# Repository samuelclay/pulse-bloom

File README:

<style>
#OB-pulse-bloom ol,
#OB-pulse-bloom ul {
    margin-left: 24px;
}
#OB-pulse-bloom li {
    color: inherit;
    font-size: inherit;
    list-style-position: outside;
}
#OB-pulse-bloom ol li {
    list-style-position: outside;
    list-style-type: decimal;
}
#OB-pulse-bloom img {
    margin: 24px auto;
    border: 1px solid #303030;
    display: block;
}
#OB-pulse-bloom img.small {
    float: left;
    margin-right: 24px;
}
#OB-pulse-bloom img.no-border {
    border: none;
}
#OB-pulse-bloom pre code {
    display: block;
    overflow-y: hidden;
}
</style>

<div id="OB-pulse-bloom">

This was my second year attending Burning Man. Many use Burning Man as a week to detach from their workweek and experience a new life of intense leisure. Not me, I come to Burning Man to build.

Pulse & Bloom is a [2014 honorarium installation](http://www.burningman.com/installations/art_honor.html). The core team of 6 people — [Saba Ghole](https://twitter.com/sabarani), [Shilo Shiv Suleman](https://twitter.com/shilo1221), [Rohan Dixit](https://twitter.com/rd108), [Heather Stewart](https://www.facebook.com/heather.stewart.3388), [Luke Iseman](https://twitter.com/liseman), and [myself](http://twitter.com/samuelclay) — built 20 interactive lotus flowers made out of steel and rowlux. Each lotus flower ranges from 8 to 18 feet tall, each of which lights up with your pulse. You and another person can put your hands on a couple of Hamsa hands at the base of the lotus flower and your respective heartbeats will light up the flower.

We've gotten some great press coverage at [the BBC](http://www.bbc.com/news/in-pictures-29059374), [The Guardian](http://www.theguardian.com/artanddesign/gallery/2014/sep/06/photography-new-york-fashion-gaza-islamic-state?CMP=fb_gu), [The Atlantic's Big Picture](http://www.theatlantic.com/infocus/2014/09/burning-man-2014/100802/#img07) [twice](http://www.theatlantic.com/infocus/2014/09/burning-man-2014/100802/#img22), [CBS News](http://www.cbsnews.com/pictures/burning-man-2014/9/), [NBC News](http://www.nbcnews.com/pop-culture/pop-culture-news/desert-dwellers-burning-man-festival-full-swing-n192541#ember903), and [MSNBC](http://on.msnbc.com/1qkUN4c).

As usual, the [complete source code for Pulse & Bloom is on GitHub](https://github.com/samuelclay/pulse-bloom).

### Your heartbeat in light

Here's a video of all twenty lotus flowers in full working order.

<video src="http://static.newsblur.com.s3.amazonaws.com/ofbrooklyn/Pulse%20%26%20Bloom.mp4" autoplay loop muted width="650"></video>

Each lotus flower is blue until a person or two sits down at its base and places their hand on the pulse sensor. You can see the Hamsa hand and its embedded pulse sensor in this shot of my girlfriend Brittany and me working on keeping the electronics going.

<h6 style="margin-top: -24px;text-align: right;">Photo credit Jim Urquhart / Reuters</h6>

When a pulse is read, the lotus flower shoots the heartbeat up the stem and into the petals, where it blooms in a brilliant display of amber. When two people's hands are being measured, both of their heartbeats are shown as two distinct colors.

## How the electronics are made

There are five stages to making the electronics:

 1. [Making the custom circuit boards](#boards)
 2. [Making the custom pulse sensors](#sensors)
 3. [Driving the high current LEDs](#leds)
 4. [Writing the firmware](#firmware)
 5. [Powering the lotuses](#power)

### 1. Making the custom circuit boards

The circuit board controls all of the lighting, sensors, timing, and debugging sequences. A reliable circuit board couldn't just be an Arduino and a breadboard. I decided to use [OSH Park](http://www.oshpark.com) and [OSH Stencils](http://www.oshstencils.com) to fabricate inexpensive circuit boards. I ultimately went through seven revisions while we worked out the final design of the lotuses. This included adding additional lights, additional sensors, controls for EL wire, and better power management using an external buck converter.

This board has support for multiple high current petal LEDs driven by digital RGB pins (used for fading colors in and out using PWM) and in multiple voltages. The high current petal LEDs runs on 12V, which comes directly off the battery, the ATmega328p chip and stem LEDs run at 5V, and the pulse sensor runs at 3.3V.

To convert 12V to 5V I use [a $3 switching voltage regulator from Electrodragon](http://www.electrodragon.com/product/better-than-lm2596-dc-dc-step-down-adjustable-power-supply-module/). This requires a +/- connection for both 12V in and 5V out. To convert 5V to 3.3V I used a linear voltage regulator soldered directly on the board, since the current requirements of the pulse sensor were around 20mA. The heat dissipated was negligible compared to the rest of the circuit.

I also added terminal connections for two 5 meter LEDs that wrapped around the tall lotus stem. We attached two 5 meter LED strips around the stems because when two people put their hands on the two pulse sensors, we need an easy way to show both heartbeats without one winning out over the other. When only one person's hand in being measured, both 5 meter light strips show the same color, which makes it that much brighter for a single person.

Lastly, the two pulse sensors terminate their I2C wires directly on the board. I used two separate I2C channels instead of one to cut down on time. I could easily have put both pulse sensors on the same I2C connections, but that would've required both pull-up resistors on the SDA and SCL data lines as well as a rewrite of the timing functions for the sensor.

All of these terminations are made using 2.5mm and 3.5mm pitch screw terminals. In hindsight I would have used female JST-SM mounted connectors and ordered custom wires with JST-SM male connectors. I assumed the lowest common denomenator would be bare tinned wire, but all of the bare wires could easily have been switched over to polarized, latching connectors. This would have reduced over 90% of the field work I had to perform on boards, as their wire would fall out of the screw terminals due to not being screwed in with enough force.

The board was laid out to be as big as a pack of gum. All of the 12V traces are thickened and isolated on the right side of the board. They are rated for 3 amps although they would end up only driving 1 amp on the playa.

These boards are then stenciled with solder paste and populated with their chips and passive components.

An inexpensive hot plate is used to reflow the solder. The chip is in a TQFP package, which has a 0.5mm pitch between pins. This makes it nearly impossible to hand solder. This stencil and reflow technique works well and my yield stayed high at around 95%.

Finally, the board is ready to be populated with screw terminals.

The final board in a dust-proof enclosure.

### 2. Making the custom pulse sensors

This was both the riskiest piece of the puzzle and also the most fun to build. In order to show your heartbeat on the lotus, I need to have a clear reading of your pulse. There are a fair number of issues with most off-the-shelf heartbeat sensors, including:

 * **Cost**: While a $50 pulse sensor is nice, it's way out of our budget. We spent $6 in components to make each of our pulse sensors for a total of 40 sensors (two per lotus).
 * **Design affordance**: There were a fair number of pulse sensors that required an infrared light on one side of your finger and an infrared detector/receiver on the other. This clamping of your finger wasn't something we could get away with in the desert. We needed a sensor you could just touch and hold on one side. It needed to be a simple interface so we wouldn't have to show any instructions.
 * **Reliability**: When a sensor gets covered in dust, will it still work? Infrared light, thankfully, passes through a layer of dust and can read the changes in blood flow in your finger. Some options were entirely visual and they would have performed quite poorly out on the playa.

The first prototype I built suffered from the design affordance and reliability issues, although it worked pretty well in ideal conditions.

<video src="http://static.newsblur.com.s3.amazonaws.com/ofbrooklyn/Pulse%20%26%20Bloom%20-%20Sensor%20opamp.mp4" autoplay loop muted width="650"></video>

We ended up finding an IC by Silicon Labs called the Si1143x, which uses three LEDs — two infrared and one visible — and a small QFN-10 sized light sensor.

I built out a small PCB the size of a fingertip.

This tiny IC is a bit tricky to solder as it has no leads and the pins are extremely close together. My yield dropped to about 80%, but 4 out of every 5 pulse sensors I built worked perfectly the first time. If they failed, I would remount them on the hot plate and try wicking away any solder bridges I could find. This worked only about half the time. After that I gave up and now have a plastic cup full of broken pulse sensors.

Finally the sensor is hooked up and a tiny red light is emitted, letting people know where to put their fingers.

### 3. Driving the high current LEDs

What turned these lotuses from flowers into gems are the high current LEDs mounted in the petals at the top. There are 9 of these high current LEDs per lotus, split into groups of three, each driven by a constant current driver. 

If you were to look at one of these LEDs from a few feet away, you would immediately see spots in your eyes. They are extremely bright pinpoints of light. The fact that they are also full color and need a heatsink due to their brightness means that you won't just find these in an easy package ready for plugging in.

<h6 style="margin-top: -24px;text-align: right;">Photo credit Jim Urquhart / Reuters</h6>

Normally a single LED is powered by a single constant current driver. This driver can drive up to 1A of current at 12V. Because we were only using a single channel of color (blue) in the rest state, which is where the lotus spent most of its time, we could triple the number of LEDs driven by a single constant current driver. 

When in use the petals glow amber, which uses two channels (100% red, 50% green) but only for a moment while at peak current. So while the peak current is above what this constant current driver is rated for, it's only at peak and therefore within our tolerance.

Using a Chinese distributor, we bought these Sparkfun high current LEDs for $0.86 each instead of the full $15. However, we also bought 80 of Sparkfun's PicoBucks to use as our constant current driver. While we could have built this ourselves to save money, buying 80 of something at $15 each is still only $1.2k, while building them ourselves would only have saved a few hundred dollars.

We bought 200 high current LEDs, all of which had to have their 6 anode and cathode connections soldered.

In order to connect 9 high current LEDs to the board, we need to drive them in groups of three. Each group has 6 connections: red, green, blue anodes, and red, green, blue cathodes. The wiring diagram for this setup can get a bit rats nesty, but the end result was fairly easy to work with, as the picobuck groups didn't cross.

Finally, a shot of a complete picobuck with the wire connectors in the background.

### 4. Writing the firmware

The [complete source code for Pulse & Bloom is on GitHub](https://github.com/samuelclay/pulse-bloom). There you can find the firmware used to program the main circuit board's ATmega328p chip, as well as designs for the laser cut cowl that sits over the pulse sensor's Si1143x IC. 

The easiest way to read the firmware is to dive into `src/pulse.cpp`. It has all of the pulse and rest states and handles the high level logic.

The state machine that runs the entire routine is determined by a couple of critical measurements. The program takes a measurement of both pulse sensors and determines whether a finger is covering either of them and whether or not that finger has an active pulse going.

    // Modes
    void determinePlayerMode();
    void determineFingerMode(int sensor1On, int sensor2On);
    void resetStem(PulsePlug *pulse);
    uint8_t adjustBpm(PulsePlug *pulse);
    
When there are no fingers on either of the pulse sensors, the program runs the rest state, which is a blue-topped lotus with a small blue snake running up and down the stem. The program is merely waiting for somebody to put their finger on a sensor.

    // State: resting
    void runResting();
    void runRestStem();
    void runRestStem(PulsePlug *pulse, int16_t currentLed);
    void clearStemLeds(PulsePlug *pulse);
    void beginPetalResting();
    bool runPetalResting();

Before a heartbeat is shown an accurate measurement of a heartbeat needs to be read. In order to determine whether a heartbeat is found and at what speed, a number of light detection measurements are taken and analyzed. I simply find the high frequency curve (the heartbeat) and the low frequency curve (the light sensors leveling out) and then use a simple peak and valley hueristic to determine the moment a heartbeat begins. This can take up to two or three seconds at first, so a bit of unwinding animation prepares you when you first put your finger on the sensor.

When a finger is detected, the stem snake lights shoot backwards up and down the lotus in prep for a heartbeat. This looks seamless as it clears the stem. This way a heartbeat doesn't interrupt the rest state.

    // State: end resting
    void beginSplittingStem();
    void runSplittingStem();
    void runSplittingStem(PulsePlug *pulse, int16_t currentLed);

When a heartbeat is detected, it is first shot up the stem. The color is determined by how many pulse sensors are being used. 1 heartbeat shows amber. 2 heartbeats show in white and light red.

    // State: stem rising
    bool runStemRising(PulsePlug *pulse, PulsePlug *shadowPulse);

Once the heartbeat reaches the top of the stem, the petals then fill with light.

    // State: petal rising
    void beginPetalRising();
    bool runPetalRising();

After a set delay, the petal slowly lose light while waiting for the next heartbeat.

    // State: petal falling
    void beginPetalFalling();
    bool runPetalFalling();

Lots of debugging messages have been left in the code and are accessible using the Serial pin on the board. Just turn on `USE_SERIAL`, which is commented out at top. Note that this increases binary code size by about 2.5K. I wrote a lot of logging.

    // Debugging
    void printHeader();
    void blink(int loops, int loopTime, bool half);
    int freeRam ();

### 5. Powering the lotuses

While much of what I built above came out of knowledge I already had, learning how to power this large of an installation off just a battery was all new to me. I'm used to microelectronics that run off a coin cell or AA batteries.

#### Measuring current and power usage

First, in order to figure out how big of a battery we needed, we had to measure how much power we were taking. I hooked up an ammeter in series with a single lotus to measure the current draw. In rest state, a single lotus drew 0.75A at 12V. In the active pulsing heartbeat state, a single lotus drew 1.5A at 12V. Since a lotus spends 95% of its time at rest, we rounded the average current consumption to 1A.

Twenty lotuses at 1A at 12V meant we needed 240Ah to sustain a 12 hour night. A car battery was recommended, but car batteries can only discharge down to 80% without irreparable harm. However, a marine deep-cycle battery can go down to 20% without harm. 

This 150 lb. battery has enough capacity, although we ended up adding a couple 6V batteries in series (to boost them to 12V) and then running them in parallel to offset some of the load.

#### Dealing with the voltage drop

A big issue we ran into was the voltage drop across the power lines. We placed the batteries on the edge of the installation, which meant some of the lotuses had 20 meters of wire between them and the battery. The voltage drop per 10 meter section is nearly 2V, which means that the voltage reaching the further lotuses was down to 7.5V. 

The high current LEDs were not able to be smoothly driven at this low of a voltage, causing them to flicker. We determined that a voltage drop was responsible for the flickering, which got worse the further the lotus sat from the batteries. But when we discovered this the wires had already been trenched 6 inches beneath the playa. A day of work lost, but we sucked it up and ripped out all of the ground wiring to accommodate the battery which had to be moved into the center of the installation.

At the end of each night we had to bike out with a trike and carry all 300 lbs. of batteries back to camp, where they were hooked up to a 1 kW solar array, where they were charged at 48A over 6 hours.

## Prototyping the lotuses

Back at American Steel in Oakland, the lotus stems, bases, and petals were ready to be hooked up. These twenty lotus stems were bent by Heather. They range from 6ft to 16ft in length and each weighs 50 lbs.

Such a heavy stem needs a larger base and heavy anchors to stay upright in the wind.

We placed the lily pad over the base to cover it up and then added all of the electronics. Lights, sensors, and circuit boards all had to be mounted.

This is a photo of our first complete lotus flower. Just compare its sheer size to Shilo.

Once we were confident that one lotus would successfully light we left the other 19 lotuses packed away for assembly on the playa.

## A dusty scene

We drove out in the biggest rental car I could get my hands on. Our minivan is full of electronics, bicycles, tents, costumes, coolers full of fruit and veggies, dry snacks, and water.

Since we were early arrival, they give you these red bracelets. They say *Work hard, don't do stupid shit*.

The boards would accumulate dust on them everyday. Our plastic enclosures turned out to be too big for the holes we made in the platform. So we ended up using ziploc bags. These baggies stayed attached, but the only reason they didn't cause any issues is that the boards worked just fine in the dust, as you can see here. 

If dust was a real problem for the boards, then I would have spent a whole lot more time making a tight fitting enclosure and a hole for it that protects it both from the elements and from people.

The playa gets covered in dust storms regularly throughout the week. A particularly nasty dust storm is pictured here, eating our poor lotus flowers alive.

Although during the day when its not dust storming the lotuses offer a cozy respite from the heat of the playa. 

<h6 style="margin-top: -24px;text-align: right;">Photo credit Jim Urquhart / Reuters</h6>

The entire process lasted 4 months with 2.5 months of nearly full-time work on my part. I'm thrilled that I get to open-source both the process and the firmware. I hope others who build art installations can use some of my lessons learned here. I'm happy to [answer any questions on Twitter](https://twitter.com/samuelclay).

See you next year on the playa!

</div>

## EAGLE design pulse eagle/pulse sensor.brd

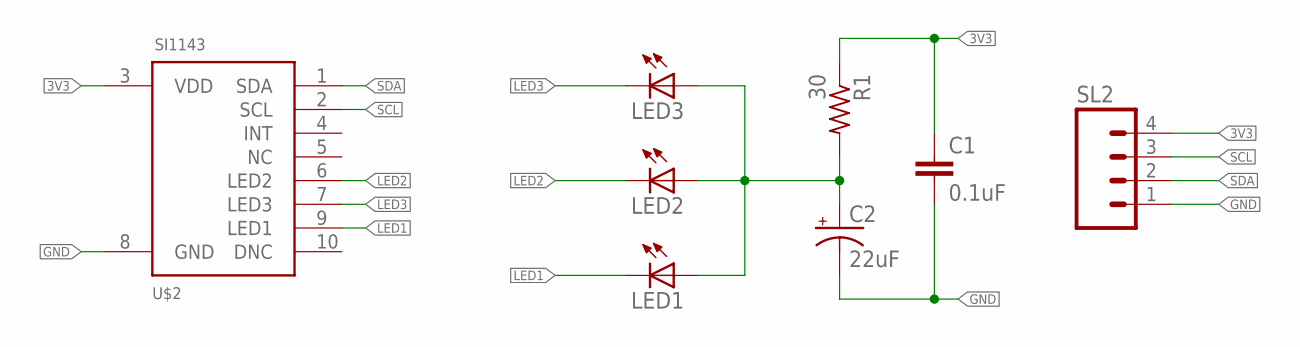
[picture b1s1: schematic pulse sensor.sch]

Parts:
C1: 0.1uF; 0402-CAP
C2: 22uF; EIA3216
LED1, LED2, LED3: LED1206; LED-1206
R1: 30; R0402
SL2: M04SMD; 1X04-SMD
U$2: SI1143

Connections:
3V3: C1.1, R1.1, SL2.4, U$2.3 (VDD)
GND: C1.2, C2.C (-), SL2.1, U$2.8 (GND)
LED1: LED1.C, U$2.9 (LED1)
LED2: LED2.C, U$2.6 (LED2)
LED3: LED3.C, U$2.7 (LED3)
unnamed: C2.A (+), LED1.A, LED2.A, LED3.A, R1.2
SCL: SL2.3, U$2.2 (SCL)
SDA: SL2.2, U$2.1 (SDA)

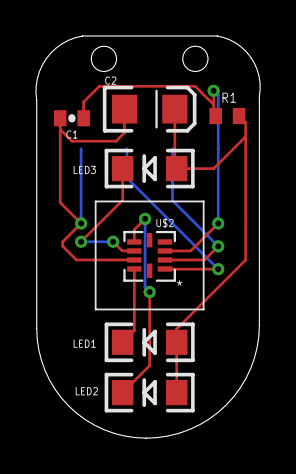
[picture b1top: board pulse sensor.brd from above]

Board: 2 copper layers, 12.5 x 22.3 mm, 8 parts (1 on the bottom side), 8 nets.

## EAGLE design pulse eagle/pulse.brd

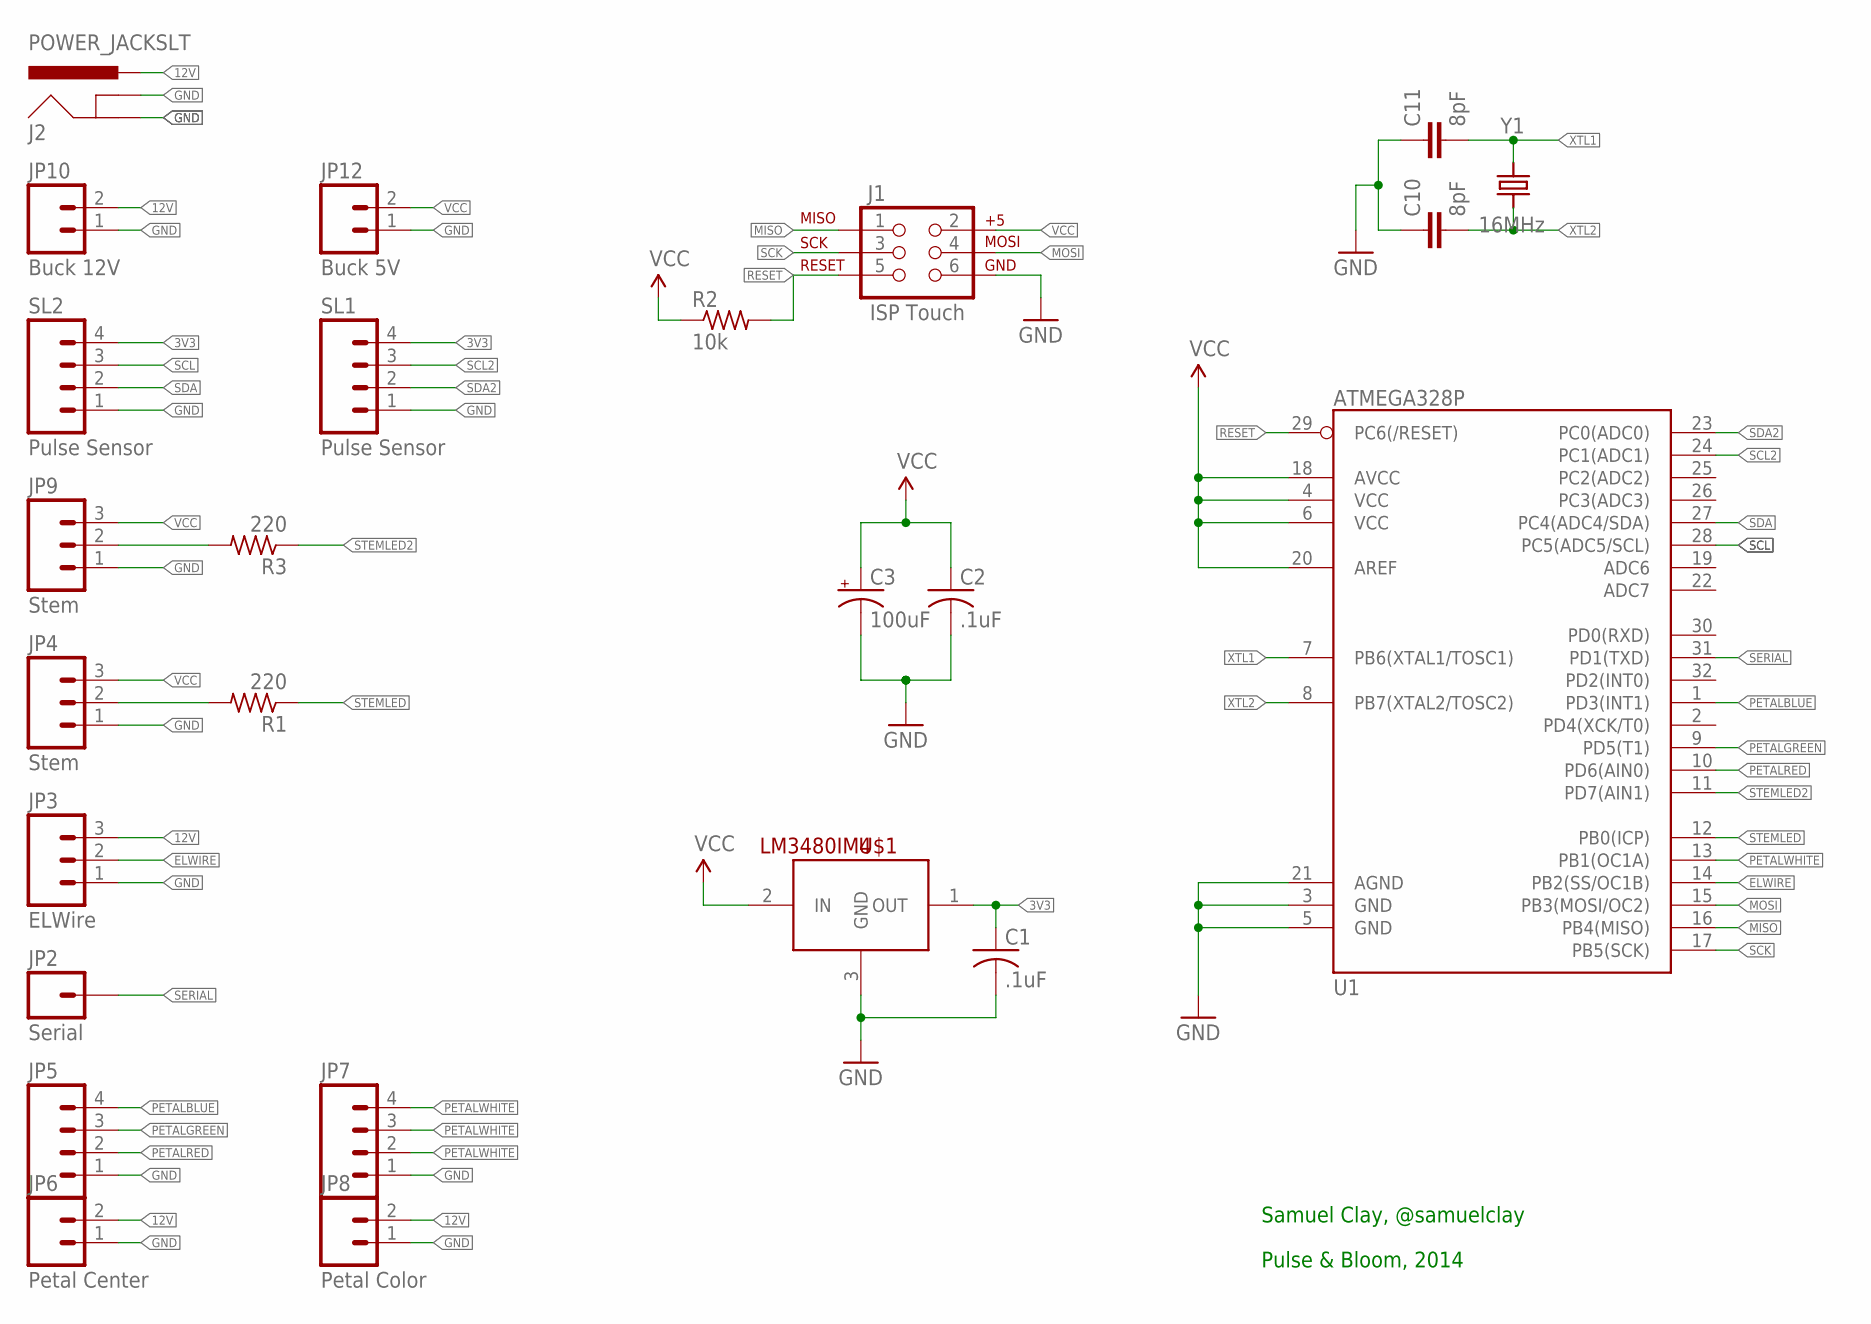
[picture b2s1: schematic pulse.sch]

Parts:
C1, C2: .1uF; C0805
C3: 100uF; EIA3216
C10, C11: 8pF; 0805
J1: ISP Touch; AVX_9188_6-WAY_MATING_GUIDE
J2: POWER_JACKSLT; POWER_JACK_SLOT
JP2: Serial; 1X01
JP3: ELWire; MOLEX-1X3_LOCK
JP4, JP9: Stem; MOLEX-1X3_LOCK
JP5: M04POLAR_LOCK; MOLEX-1X4_LOCK
JP6: Petal Center; SCREWTERMINAL-3.5MM-2_LOCK
JP7: M04POLAR; MOLEX-1X4
JP8: Petal Color; SCREWTERMINAL-3.5MM-2_LOCK
JP10: Buck 12V; SCREWTERMINAL-3.5MM-2_LOCK
JP12: Buck 5V; SCREWTERMINAL-3.5MM-2_LOCK
R1, R3: 220; R0805
R2: 10k; R0805
SL1, SL2: Pulse Sensor; MOLEX-1X4_LOCK
U1: ATMEGA328P; TQFP32-08
U$1: LM3480IM4; SOT23-3
Y1: 16MHz; NX5032GA

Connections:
3V3: C1.1, SL1.4, SL2.4, U$1.1 (OUT)
12V: J2.PWR, JP3.3, JP6.2, JP8.2, JP10.2
ELWIRE: JP3.2, U1.14 (PB2(SS/OC1B))
GND: C1.2, C2.2, C3.C (-), C10.1, C11.1, J1.6, J2.GND@1 (GNDBREAK), J2.GND@2 (GND), JP3.1, JP4.1, JP5.1, JP6.1, JP7.1, JP8.1, JP9.1, JP10.1, JP12.1, SL1.1, SL2.1, U1.3 (GND), U1.5 (GND), U1.21 (AGND), U$1.3 (GND)
MISO: J1.1, U1.16 (PB4(MISO))
MOSI: J1.4, U1.15 (PB3(MOSI/OC2))
unnamed: JP9.2, R3.2
unnamed: JP4.2, R1.2
PETALBLUE: JP5.4, U1.1 (PD3(INT1))
PETALGREEN: JP5.3, U1.9 (PD5(T1))
PETALRED: JP5.2, U1.10 (PD6(AIN0))
PETALWHITE: JP7.2, JP7.3, JP7.4, U1.13 (PB1(OC1A))
RESET: J1.5, R2.2, U1.29 (PC6(/RESET))
SCK: J1.3, U1.17 (PB5(SCK))
SCL: SL2.3, U1.28 (PC5(ADC5/SCL))
SCL2: SL1.3, U1.24 (PC1(ADC1))
SDA: SL2.2, U1.27 (PC4(ADC4/SDA))
SDA2: SL1.2, U1.23 (PC0(ADC0))
SERIAL: JP2.1, U1.31 (PD1(TXD))
STEMLED: R1.1, U1.12 (PB0(ICP))
STEMLED2: R3.1, U1.11 (PD7(AIN1))
VCC: C2.1, C3.A (+), J1.2, JP4.3, JP9.3, JP12.2, R2.1, U1.4 (VCC), U1.6 (VCC), U1.18 (AVCC), U1.20 (AREF), U$1.2 (IN)
XTL1: C11.2, U1.7 (PB6(XTAL1/TOSC1)), Y1.P$2 (2)
XTL2: C10.2, U1.8 (PB7(XTAL2/TOSC2)), Y1.P$1 (1)

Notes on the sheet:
Samuel Clay, @samuelclay
Pulse & Bloom, 2014

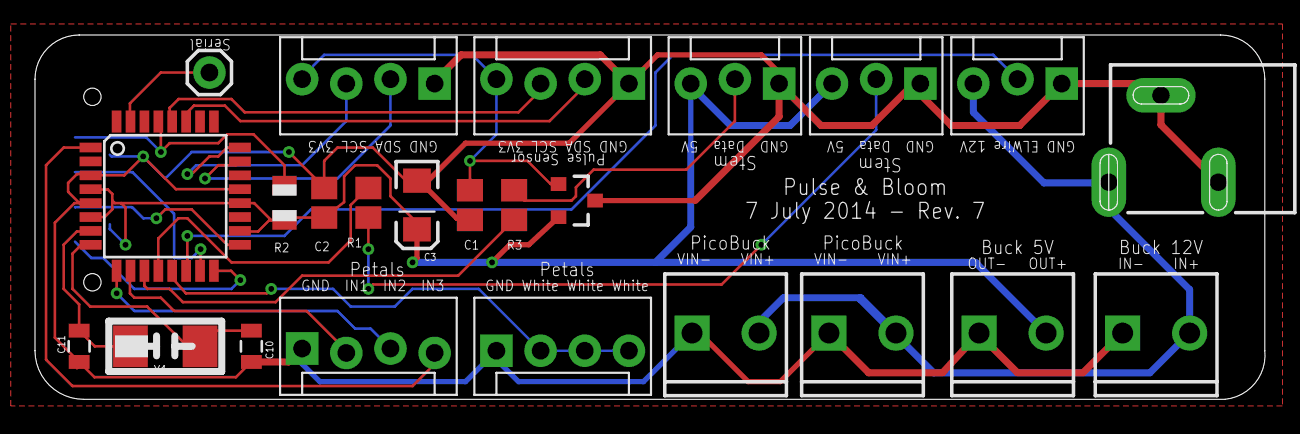
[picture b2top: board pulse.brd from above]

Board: 2 copper layers, 70.8 x 21.0 mm, 25 parts (1 on the bottom side), 24 nets.

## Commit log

2014-04-28 Initial commit of prototype heartbeat sensor.
2014-05-03 Updating seiral monitor.
2014-05-04 Smoothing, counting, and calculating an online median for the new sampler.
2014-05-04 Heartbeat indicator now calibrated. Just need to move period around.
2014-05-04 Refactoring to fix sizes. Still firing too often, needs peaking logic worked out.
2014-05-06 Rearranging into build/src/libs.
2014-05-06 Much better pulse detection. Now just need to fill in missed pulses.
2014-05-06 Faking time (at a 100ms delay) when pulse isn't detected.
2014-05-06 Much happier with the math. No longer tossing top and bottom 15% of samples, as it was slowing down collection.
2014-05-09 Eagle schematic. Needs values, but hookups are all correct.
2014-05-10 Finished board layout at .8"x1.25". Needs labels, then it's ready to print!
2014-05-10 Invoking power/ground on op amp, fixing dimension, drawing polarized lines for tantalum caps, and adjusting labels.
2014-05-10 Fixing the last few silkscreen placement lines. Adjusting schematic.
2014-05-10 Adding serial port headers.
2014-05-30 Rev. A of the board.
2014-06-01 Moving pins around.
2014-06-01 Showing faked data. Also moving pins around.
2014-06-10 Rev. 2 of the board, with new headers for el wire, led data, and pwm led.
2014-06-10 Adjusting sampling, moving pins around, adding fade.
2014-06-10 Preparing for a slow down of speeds.
2014-06-10 Adding Neopixel.
2014-06-10 Fixing glitchy colors on led stem.
2014-06-11 Switching from attiny84 to atmega328 for the hardware serial, bigger flash size, additional PWMs, and negligible package size difference.
2014-06-11 Handling fake heartbeats better. Still needs work.
2014-06-19 Switch from crappy IR sensors to SI1143 IC.
2014-06-19 Adding library for Eagle with SI1143 component.
2014-06-19 Re-orienting and preparing board for layout.
2014-06-20 Ripping out all of my code in place of the new Si1143 sensor. Need to add back in strip and petal led logic.
2014-06-21 Revision 4 of the board now connects all 5v, 12v, and 3.3v devices. Revision 1 of the sensor board.
2014-06-21 Pulse Sensor board.
2014-06-23 Adding extra stem led and three extra petal leds. Needs routing.
2014-06-23 Reading new pulse sensor and sending down pulses.
2014-06-23 Fixing pulse sensor bug where it only works after a reset. Why, I don't know, but this works pretty well.
2014-06-24 Stem now animates smoothly at an adjustable pulse width. Petal now glows, even after the next pulse has started.
2014-06-24 Revision 5 of the board, with 4 x Petals, 2 x Stem.
2014-06-24 Adding extra gnd pins for picobucks. probably going to need more picobucks.
2014-06-24 Got it. The petals are now mesmerizing. Multiple pulse on the petals now build on each other.
2014-06-24 Adding second pulse sensor to board and code. Need to write code to handle second pulse sensor and second stem.
2014-06-25 Abstracted out pulse sensors so that multiple pulse sensors can control multiple strips. Crashes when second pulse sensor is used.
2014-06-25 Fixing memory issues by moving neopixel strip to local functions to reclaim RAM.
2014-06-26 Cleaning up a bit.
2014-07-08 Switching out TQFP for DIP package.
2014-07-08 Adding a barrel jack and proper buck converter connectors.
2014-07-08 Adding easing functions.
2014-07-08 Easing library.
2014-07-09 Adding resting state when nobody is at lotus.
2014-07-09 Refactoring pulse sensor. Fixing issues around having one or the other pulse sensor turned on.
2014-07-15 Resting state now using cylons and uses both stem leds.
2014-07-16 Fixing bug where a pulse before the pulse decay time would not clear the resting state.
2014-07-16 Perfecting the petal fade and fixing issues when using two sensors and having the petal bounce.
2014-07-16 Cleaning up ambiguous variable names. Cleaning up warnings.
2014-07-16 Fixing lingering brightness issues.
2014-07-16 The big one. Heartbeats are now faked with real heartbeats quickly pushing faked data into correct data. Looks great and has few false positives.
2014-07-17 Revision 2 of the pulse sensor. Upgrading to tantalum cap, switching the two caps, and using the correct resistor value. Also switching to temrinal connectors on bottom of board.
2014-07-23 Fixing initial programming with correct optimization flag.
2014-07-23 Stubbing in ground lights.
2014-07-26 Fixing petal led brightness reset glitch when multiple pulses are running.
2014-08-01 Fixing pulse sensor to use new leds.
2014-08-01 Adding sketchup model for cowl.
2014-08-02 Instant finger detection. Works when a finger is new and when a finger leaves.
2014-08-02 A beautiful effect. When a new finger touches the sensor, the resting animation quickly winds backwards, turning into heartbeats.
2014-08-02 Christ this effect is delightful. Tuning smoothing.
2014-08-02 Better colors.
2014-08-04 Adding cowl OBJ file for printing.
2014-08-10 Slowing down pulse going up stem. Also changing colors.
2014-08-10 Gradients in rest state.
2014-08-11 Fixing bug where the rest split state would run when a finger was lifted during stem rise.
2014-08-11 Improved heart beat pacing. Also fixing second premature splitting issue.
2014-08-11 Cleaning up serial debugging for fewer instructions per clock cycle.
2014-08-11 Prettifying
2014-08-11 When moving to double fingers, possibly freezing of stem leds.
2014-08-11 Nicer 2 person colors.
2014-08-11 Speeding up split lag time by taking the pivot point into account.
2014-08-11 Removing warning.
2014-08-13 Adding petal led delay to make the petals stay bright for a tenth of a second longer.
2014-08-13 Adding wiring diagram in OmniGraffle.
2014-08-14 Setting off petals when stem gets interrupted.
2014-08-14 Adding petal landing and landed state.
2014-08-14 Adding state for the resting and awakening of the petal colors.
2014-08-15 Fixing obnoxious petal blink when petal is told to rise while already rising.
2014-08-20 Adding RGB intro sequence. I hope to never see this during use, only startup.
2014-08-23 Handling missing pulse sensor.
2014-08-24 Star pattern rest state.
2014-09-04 Adding video and images for blogging.
2014-09-05 Adding media and outlining.
2014-09-05 Custom boards.
2014-09-05 Sensors and LEDs.
2014-09-05 Blogged the battery section.
2014-09-05 Wrote out prototyping and conclusion. Needs a good proofreading.
2014-09-08 Update and rename README.md to README
2014-09-08 Rename README to README.md
2014-09-08 Writing README
2014-09-08 .DS_Store = OS X detritus
2014-09-08 .gitignore cleanup
2014-09-09 Adding modern device header.
2014-12-20 commiting changes by sam during burning man 2014
2015-09-02 Proofed and revised. Ready to post.
2015-09-02 Adding hex file.
2015-09-02 Rebuilding hex file.
2016-08-05 Petal LEDs pdf.
2023-04-11 Adding installation to readme

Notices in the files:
parts and their libraries:
SparkFun-LED: Licensing: CC v3.0 Share-Alike You are welcome to use this library for commercial purposes.
